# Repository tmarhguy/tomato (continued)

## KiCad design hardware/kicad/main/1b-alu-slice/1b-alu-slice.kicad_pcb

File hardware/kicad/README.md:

# Tomato — KiCad

<p align="center"><strong>Numbered PCB lots for the 32-bit Dual-LUT machine.</strong></p>

Physical boards for Tomato. Logic authority stays in [Digital](../digital/README.md); these projects are fab and assembly. Lot **07** (`07_alu`) is on the iron.

**Project map:** [Hardware](../README.md) · [Boards](boards/README.md) · [07_alu doc](boards/07_alu/README.md) · Paper: [boards.html](https://tomato.tmarhguy.com/boards.html)

<p align="center"><em>Lot 07 in the round &amp; on the iron · Dual-LUT slice · <a href="boards/07_alu/README.md">board doc</a></em></p>

<p align="center"><em>Left: board render · Right: routed top copper</em></p>

```
kicad/
├── boards/     # 01_alu … 08_display — numbered lots
├── modules/    # Reusable subcircuits
└── README.md
```

| Lot | Path | Role | Status |
|-----|------|------|--------|
| 01 | [01_alu/](boards/01_alu/) | Early ALU experiments | Historical |
| 02 | [02_shift_encoder/](boards/02_shift_encoder/) | Shift encoder + mul-div control | In design |
| 03 | [03_memory/](boards/03_memory/) | Memory, byte-lane, VGA | In design |
| 04 | [04_register/](boards/04_register/) | Register file, IR | In design |
| 05 | [05_program_counter/](boards/05_program_counter/) | PC, stack pointer | In design |
| 06 | [06_data_bus/](boards/06_data_bus/) | Data bus, wb_mux | In design |
| 07 | [07_alu/](boards/07_alu/) | Dual-LUT ALU PCB | **Populating** |
| 08 | [08_alu_fsm/](boards/08_alu_fsm/), [08_display/](boards/08_display/) | FSM bring-up, display | In design |

---

## Legacy — 8-bit transistor ALU (pre-Tomato)

> The notes below document the earlier discrete-transistor / modular board story (270×270 mm class designs, `main_logic`, `add_sub`, …). Paths and inventory there are **historical**. Living Tomato copper is the numbered lots above; Lot 07 is the Dual-LUT slice.

### KiCad PCB Design Files

**Complete hardware design for the 8-bit discrete transistor ALU**

This directory contains all KiCad schematic and PCB layout files for fabrication-ready hardware.

---

## Directory Structure

```
kicad/
├── boards/              # Complete board designs
│   ├── alu/             # Main 270×270mm ALU board (if monolithic)
│   ├── add_sub/         # Add/subtract module
│   ├── flags/           # Flag generation circuit
│   ├── main_control/    # Control decoder
│   ├── main_logic/      # Logic unit
│   └── led_panel/       # Display panels
├── modules/             # Reusable subcircuits
│   ├── gates/           # Logic gate implementations
│   ├── adder/           # Adder circuits (1-bit, 2-bit, 8-bit)
│   └── mux/             # Multiplexer modules
└── README.md            # This file
```

---

## Main ALU Board

**Design:** 270mm × 270mm combinational logic processor

### Specifications

| Parameter | Value |
|-----------|-------|
| **Board Size** | 270mm × 270mm (10.6" × 10.6") |
| **Layers** | 2 (signal + ground) |
| **Transistors** | 3,488 (Hybrid: Discrete + equivalent ICs) |
| **Technology** | 5V logic, NMOS/PMOS pairs |
| **Power** | 5V @ 0.5-1A |
| **I/O** | 22 pins (8× A, 8× B, 5× FUNC, 1× GND) |
| **Outputs** | 12 pins (8× OUT, 4× FLAGS) |

### Board Sections

1. **Arithmetic Unit** (top-left)
   - 8-bit ripple-carry adder
   - XOR array for B input
   - 432 transistors

2. **Logic Unit** (top-right)
   - NAND/NOR/XOR arrays
   - PASS A/B buffers
   - 5:1 MUX
   - 352 transistors

3. **Selection Logic** (center)
   - 2:1 MUX (arithmetic vs logic)
   - Global inverter
   - 176 transistors

4. **Flag Generation** (bottom-left)
   - EQUAL comparator
   - LESS comparator
   - POSITIVE detector
   - COUT routing
   - ~240 transistors

5. **Control Decoder** (bottom-right)
   - FUNC[4:0] opcode decoder
   - Control signal generation
   - ~68 transistors

*Figure 1 - Main ALU logic board: 270×270mm with 3,488 transistors (Hybrid)*

**Evidence:** Physical PCB fabricated and assembled.

---

## File Formats

### KiCad Project Files

| Extension | Purpose | Version Control |
|-----------|---------|-----------------|
| `.kicad_pro` | Project settings | Track |
| `.kicad_sch` | Schematic | **Track (critical)** |
| `.kicad_pcb` | PCB layout | **Track (critical)** |
| `.kicad_sym` | Custom symbols | Track |
| `.kicad_mod` | Custom footprints | Track |
| `-backups/` | Auto-backups | Ignore |
| `fp-info-cache` | Footprint cache | Ignore |

### Export Formats

| Format | Purpose | Location |
|--------|---------|----------|
| **PDF** | Documentation | Export as needed |
| **SVG** | Vector schematics | `../../web/assets/schematics photos svg/` |
| **Gerber** | Manufacturing | Generated on demand |
| **BOM** | Component list | `docs/build-notes/bom.md` |
| **STEP** | 3D mechanical | `web/glb exports/` |

---

## Board Designs

### Main Logic Board

**File:** `boards/main_logic/main_logic.kicad_sch`

*Figure 2 - Complete main logic schematic*

**Key Components:**
- 624 discrete transistors (plus 2,864 in ICs)
- 74HC157 2:1 MUX (2×)
- Power distribution network
- I/O headers

**Interfaces:**
```
Inputs:  A[7:0], B[7:0], FUNC[4:0], VCC, GND
Outputs: OUT[7:0], LESS, EQUAL, POSITIVE, COUT
```

**Evidence:** Complete schematic shows all signal paths.

### Add/Sub Module

**File:** `boards/add_sub/add_sub.kicad_sch`

*Figure 3 - Add/subtract module with XOR array*

**Function:** Conditional B inversion for subtraction

**Components:**
- 8× XOR gates (96T)
- M control signal routing

**Logic:** B' = B XOR M

**Evidence:** XOR array enables efficient ADD/SUB implementation.

### Flags Board

**File:** `boards/flags/flags.kicad_sch`

*Figure 4 - Flag generation circuit*

**Flags generated:**
- EQUAL: A == B comparator (~100T)
- LESS: A < B magnitude comparator (~120T)
- POSITIVE: (OUT > 0) detector (~20T)
- COUT: Carry out routing (0T)

**Evidence:** Dedicated flag logic provides comparison results.

### Control Unit

**File:** `boards/main_control/main_control.kicad_sch`

*Figure 5 - Control unit opcode decoder*

**Function:** FUNC[4:0] → {M, MUX_SEL, INV_OUT, LOGIC_SEL}

**Implementation:** Combinational decode logic (~68T)

**Evidence:** Control decoder translates opcodes to internal control signals.

---

## PCB Design Process

### Step 1: Schematic Capture

*Figure 6 - Schematic capture in KiCad*

**Process:**
1. Create hierarchical design
2. Place components
3. Wire connections
4. Add power symbols
5. Annotate references
6. Run ERC (Electrical Rules Check)

### Step 2: PCB Layout

*Figure 7 - PCB layout for ALU*

**Process:**
1. Import netlist
2. Define board outline (270×270mm)
3. Place components strategically
4. Route power rails (wide traces)
5. Route signals
6. Add ground plane
7. Run DRC (Design Rules Check)

### Step 3: Routing

*Figure 8 - Click to watch: PCB routing demonstration*

**Routing strategy:**
- Power rails first (1mm+ traces)
- Critical signals (clock-free, so no priority)
- Minimize via count
- Maintain trace spacing (0.2mm min)

**Evidence:** Routing video shows systematic layout approach.

---

## Manufacturing

### Gerber Generation

**Process:**
```
KiCad → File → Fabrication Outputs → Gerbers
```

**Generated files:**
- Copper layers (Top, Bottom)
- Solder mask layers
- Silkscreen layers
- Drill files (.drl)
- Board outline

### PCB Ordering

**Recommended manufacturers:**
- **JLCPCB** - Economical, good quality
- **PCBWay** - Higher quality options
- **OSH Park** - USA-based, excellent quality

**Specifications to provide:**
- Board size: 270×270mm
- Layers: 2
- Thickness: 1.6mm
- Copper: 1oz
- Surface finish: HASL lead-free
- Silkscreen: White on green

---

## Assembly Notes

### Component Placement Order

1. **Smallest first:** Resistors, capacitors (if SMD)
2. **Transistors:** 3,488 total (624 Discrete pairs + 74xx ICs + Support)
3. **ICs:** 74HC157 multiplexers (use sockets)
4. **Headers:** I/O connectors
5. **LEDs:** Output indicators (last)

### Soldering Tips

- **Temperature:** 320-350°C for lead-free solder
- **Tip size:** Fine chisel (1-2mm) for transistor leads
- **Flux:** Use liberally for better flow
- **Inspection:** Magnification recommended
- **Testing:** Test subsystems before full integration

*Figure 9 - Component placement before soldering*

*Figure 10 - Hand soldering transistors (Total count: 3,488)*

**Evidence:** Assembly process documented step-by-step.

---

## Design Files

### Opening in KiCad

```bash
cd schematics/kicad/boards/main_logic
kicad main_logic.kicad_pro
```

**KiCad version:** 9.0.6 or later required

### Exporting

**Schematic PDF:**
```
File → Plot → Plot format: PDF
```

**Schematic SVG:**
```
File → Plot → Plot format: SVG
```

**PCB 3D View:**
```
View → 3D Viewer → File → Export → STEP
```

---

## References

- [Board Documentation](boards/README.md) - Individual board details
- [Modules](modules/README.md) - Reusable subcircuits
- [Architecture](../../docs/ARCHITECTURE.md) - System architecture
- [BOM](../../docs/build-notes/bom.md) - Bill of materials

---

**Last Updated:** 2026-01-16  
**KiCad Version:** 9.0.6+  
**Board Count:** 8 designs  
**Status:** Fabrication-ready

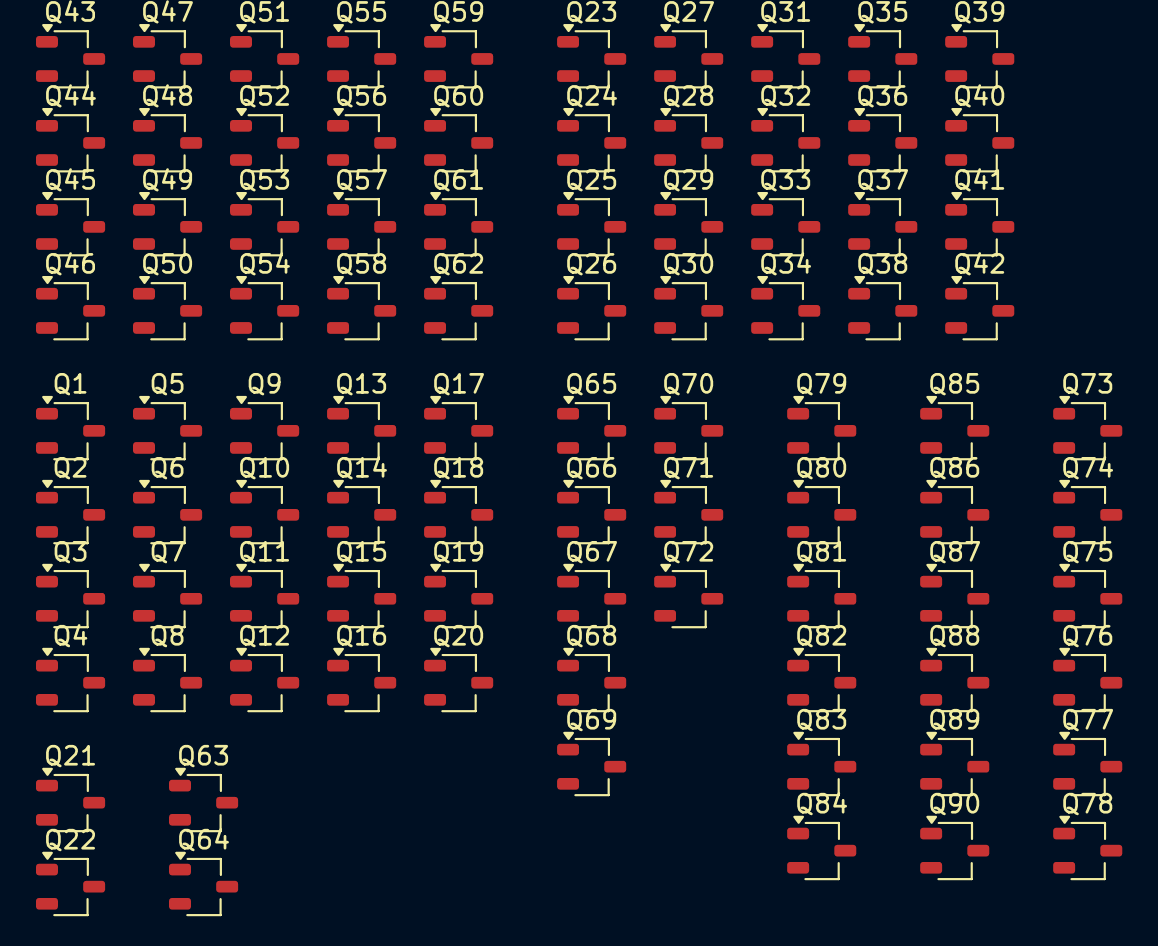
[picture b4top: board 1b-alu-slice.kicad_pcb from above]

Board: 2 copper layers, 90 parts (0 on the bottom side), 49 nets, no tracks yet.

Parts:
Q1, Q3, Q6, Q8, Q10, Q12, Q14, Q16, Q17, Q19, Q21, Q23, Q25, Q28, Q30, Q32, Q34, Q36, Q38, Q39, Q41, Q43, Q45, Q48, Q50, Q52, Q54, Q56, Q58, Q59, Q61, Q63, Q65, Q67, Q71, Q73, Q74, Q79, Q80, Q86, Q87, Q89: Q_PMOS; TSOT-23
Q2, Q4, Q5, Q7, Q9, Q11, Q13, Q15, Q18, Q20, Q22, Q24, Q26, Q27, Q29, Q31, Q33, Q35, Q37, Q40, Q42, Q44, Q46, Q47, Q49, Q51, Q53, Q55, Q57, Q60, Q62, Q64, Q66, Q68, Q69, Q70, Q72, Q75, Q76, Q81, Q82, Q85, Q88, Q90: Q_NMOS; TSOT-23
Q77, Q83: PMOS; TSOT-23
Q78, Q84: NMOS; TSOT-23

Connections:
/A: Q5.3 (S), Q6.3 (S), Q21.2 (G), Q22.2 (G)
/A_SEL[0]: Q1.2 (G), Q2.2 (G), Q14.2 (G), Q15.2 (G)
/A_SEL[1]: Q3.2 (G), Q4.2 (G), Q6.2 (G), Q7.2 (G), Q10.2 (G), Q11.2 (G)
/B: Q47.3 (S), Q48.3 (S), Q63.2 (G), Q64.2 (G)
/B_SEL[0]: Q43.2 (G), Q44.2 (G), Q56.2 (G), Q57.2 (G)
/B_SEL[1]: Q45.2 (G), Q46.2 (G), Q48.2 (G), Q49.2 (G), Q52.2 (G), Q53.2 (G)
/CIN: Q67.2 (G), Q68.2 (G), Q70.1 (D), Q73.2 (G), Q76.2 (G)
/COUT: Q89.1 (D), Q90.1 (D)
/FUNC[0]: Q27.3 (S), Q28.3 (S)
/FUNC[1]: Q29.3 (S), Q30.3 (S)
/FUNC[2]: Q31.3 (S), Q32.3 (S)
/FUNC[3]: Q33.3 (S), Q34.3 (S)
/LOGIC_OUT: Q41.1 (D), Q42.1 (D), Q65.2 (G), Q66.2 (G), Q70.2 (G), Q74.2 (G), Q75.2 (G)
/S: Q71.1 (D), Q72.1 (D)
/and1/Y: Q77.1 (D), Q78.1 (D), Q85.2 (G), Q86.2 (G)
/and2/A: Q25.2 (G), Q26.2 (G), Q28.2 (G), Q29.2 (G), Q32.2 (G), Q33.2 (G), Q61.1 (D), Q62.1 (D), Q79.2 (G), Q82.2 (G)
/and2/B: Q19.1 (D), Q20.1 (D), Q23.2 (G), Q24.2 (G), Q36.2 (G), Q37.2 (G), Q80.2 (G), Q81.2 (G)
/and2/Y: Q83.1 (D), Q84.1 (D), Q87.2 (G), Q88.2 (G)
/inv1/Y: Q7.3 (S), Q8.3 (S), Q21.1 (D), Q22.1 (D)
/inv2/Y: Q49.3 (S), Q50.3 (S), Q63.1 (D), Q64.1 (D)
GND: Q2.3 (S), Q4.3 (S), Q11.3 (S), Q12.3 (S), Q18.3 (S), Q20.3 (S), Q22.3 (S), Q24.3 (S), Q26.3 (S), Q40.3 (S), Q42.3 (S), Q44.3 (S), Q46.3 (S), Q53.3 (S), Q54.3 (S), Q60.3 (S), Q62.3 (S), Q64.3 (S), Q66.3 (S), Q68.3 (S), Q72.3 (S), Q76.3 (S), Q78.3 (S), Q82.3 (S), Q84.3 (S), Q85.3 (S), Q88.3 (S), Q90.3 (S)
unnamed: Q1.1 (D), Q2.1 (D), Q13.2 (G), Q16.2 (G)
unnamed: Q9.1 (D), Q10.1 (D), Q11.1 (D), Q12.1 (D), Q15.3 (S), Q16.3 (S)
unnamed: Q3.1 (D), Q4.1 (D), Q5.2 (G), Q8.2 (G), Q9.2 (G), Q12.2 (G)
unnamed: Q13.1 (D), Q14.1 (D), Q15.1 (D), Q16.1 (D), Q17.2 (G), Q18.2 (G)
unnamed: Q5.1 (D), Q6.1 (D), Q7.1 (D), Q8.1 (D), Q13.3 (S), Q14.3 (S)
unnamed: Q17.1 (D), Q18.1 (D), Q19.2 (G), Q20.2 (G)
unnamed: Q23.1 (D), Q24.1 (D), Q35.2 (G), Q38.2 (G)
unnamed: Q25.1 (D), Q26.1 (D), Q27.2 (G), Q30.2 (G), Q31.2 (G), Q34.2 (G)
unnamed: Q27.1 (D), Q28.1 (D), Q29.1 (D), Q30.1 (D), Q35.3 (S), Q36.3 (S)
unnamed: Q31.1 (D), Q32.1 (D), Q33.1 (D), Q34.1 (D), Q37.3 (S), Q38.3 (S)
unnamed: Q35.1 (D), Q36.1 (D), Q37.1 (D), Q38.1 (D), Q39.2 (G), Q40.2 (G)
unnamed: Q39.1 (D), Q40.1 (D), Q41.2 (G), Q42.2 (G)
unnamed: Q43.1 (D), Q44.1 (D), Q55.2 (G), Q58.2 (G)
unnamed: Q45.1 (D), Q46.1 (D), Q47.2 (G), Q50.2 (G), Q51.2 (G), Q54.2 (G)
unnamed: Q47.1 (D), Q48.1 (D), Q49.1 (D), Q50.1 (D), Q55.3 (S), Q56.3 (S)
unnamed: Q51.1 (D), Q52.1 (D), Q53.1 (D), Q54.1 (D), Q57.3 (S), Q58.3 (S)
unnamed: Q55.1 (D), Q56.1 (D), Q57.1 (D), Q58.1 (D), Q59.2 (G), Q60.2 (G)
unnamed: Q59.1 (D), Q60.1 (D), Q61.2 (G), Q62.2 (G)
unnamed: Q65.1 (D), Q66.1 (D), Q69.2 (G)
unnamed: Q67.1 (D), Q68.1 (D), Q69.3 (S)
unnamed: Q69.1 (D), Q70.3 (S), Q71.2 (G), Q72.2 (G)
unnamed: Q73.1 (D), Q74.1 (D), Q75.1 (D), Q77.2 (G), Q78.2 (G)
unnamed: Q75.3 (S), Q76.1 (D)
unnamed: Q79.1 (D), Q80.1 (D), Q81.1 (D), Q83.2 (G), Q84.2 (G)
unnamed: Q81.3 (S), Q82.1 (D)
unnamed: Q85.1 (D), Q87.1 (D), Q88.1 (D), Q89.2 (G), Q90.2 (G)
unnamed: Q86.1 (D), Q87.3 (S)
VCC: Q1.3 (S), Q3.3 (S), Q9.3 (S), Q10.3 (S), Q17.3 (S), Q19.3 (S), Q21.3 (S), Q23.3 (S), Q25.3 (S), Q39.3 (S), Q41.3 (S), Q43.3 (S), Q45.3 (S), Q51.3 (S), Q52.3 (S), Q59.3 (S), Q61.3 (S), Q63.3 (S), Q65.3 (S), Q67.3 (S), Q71.3 (S), Q73.3 (S), Q74.3 (S), Q77.3 (S), Q79.3 (S), Q80.3 (S), Q83.3 (S), Q86.3 (S), Q89.3 (S)
